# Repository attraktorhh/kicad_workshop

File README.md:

# KiCAD Workshop

Slides und Proketdateien für den Workshop 'Platinendesign mit KiCAD'

## Ablauf

Der Workshop finded in 3 Teilen statt.

### Teil 1

Im ersten Teil wird der Schaltplan erstellt und Footprints zugeordnet.

### Teil 2

Bei zweiten Workshop wird aus dem Schaltplan, der in Teil 1 erstellt wurde, eine Platine designed.

### Teil 3

Bein dritten Termin dreht sich alles um die Erstellung von Produktionsdateien (Gerber, BOM, Pick&Place).

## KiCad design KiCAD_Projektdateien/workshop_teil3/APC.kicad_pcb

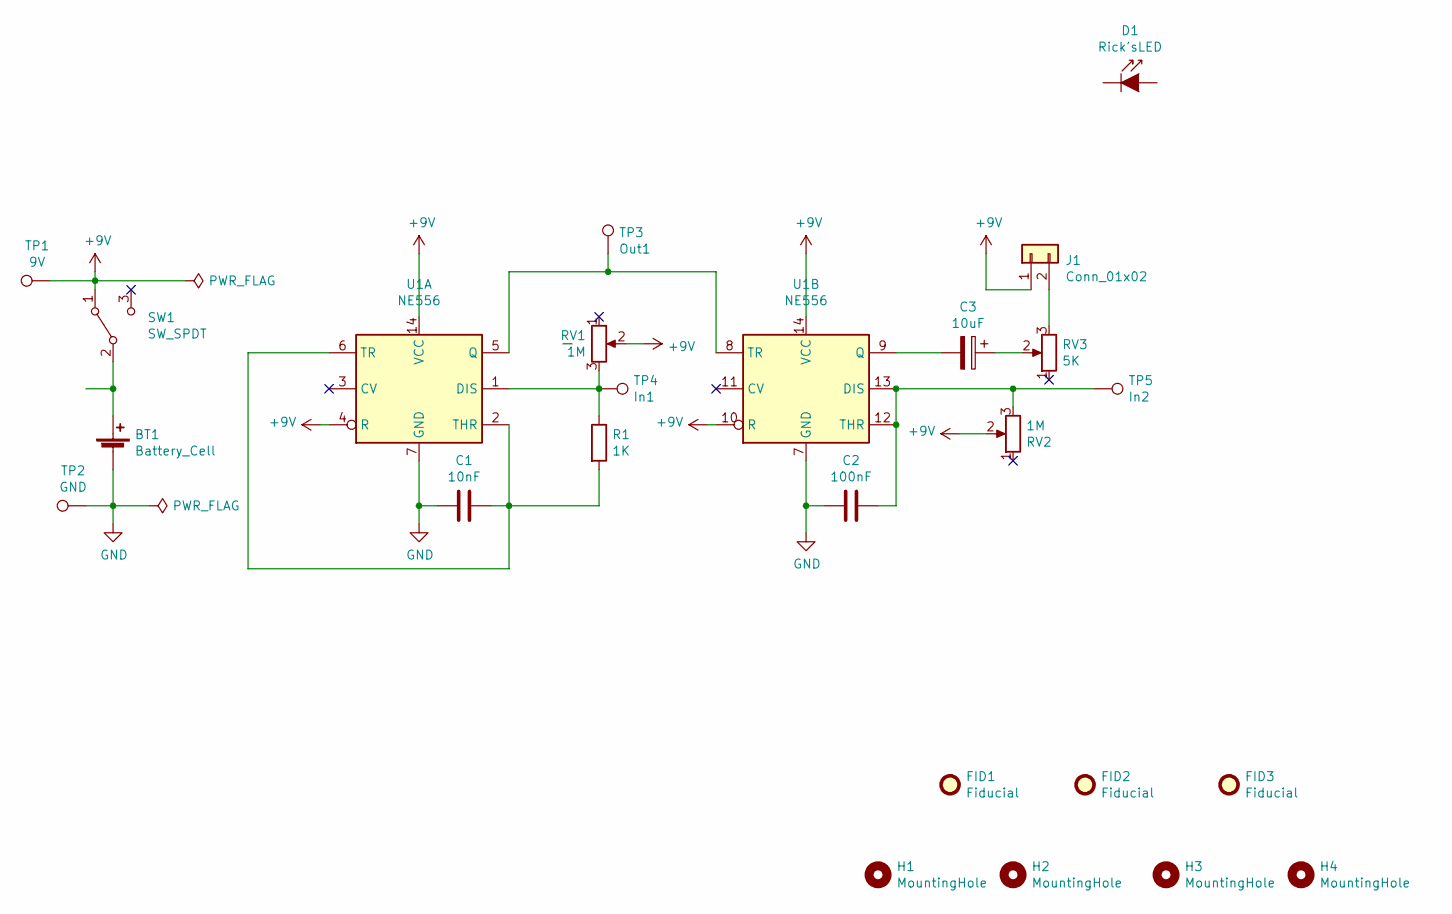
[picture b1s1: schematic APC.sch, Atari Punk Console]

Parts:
BT1: Battery_Cell; BatteryHolder_Eagle_12BH611-GR; Part Nr. 12BH611-GR
C1: 10nF; C_0603_1608Metric_Pad1.05x0.95mm_HandSolder; Part Nr. 885012206040
C2: 100nF; C_0603_1608Metric_Pad1.05x0.95mm_HandSolder; Part Nr. 885012206046
C3: 10uF; CP_Elec_5x3; Part Nr. 865080340001
D1: Rick'sLED; SOIC-12
FID1, FID2, FID3: Fiducial; Fiducial_1mm_Mask2mm
H1, H2, H3, H4: MountingHole; MountingHole_3.2mm_M3
J1: Conn_01x02; SolderWirePad_1x02_P7.62mm_Drill2.5mm
R1: 1K; R_0603_1608Metric_Pad1.05x0.95mm_HandSolder; Part Nr. ERJ-U02D7500X
RV1, RV2: 1M; Potentiometer_Bourns_PTV09A-1_Single_Vertical; Part Nr. PTV09A-4020U-B504
RV3: 5K; Potentiometer_Bourns_PTV09A-1_Single_Vertical; Part Nr. PTV09A-4020F-A502
SW1: SW_SPDT; SW_SPDT_CK-JS102011SAQN; Part Nr. JS102011SAQN
TP1: 9V; TestPoint_Pad_D1.5mm
TP2: GND; TestPoint_Pad_D1.5mm
TP3: Out1; TestPoint_Pad_D1.5mm
TP4: In1; TestPoint_Pad_D1.5mm
TP5: In2; TestPoint_Pad_D1.5mm
U1: NE556; SOIC-14_3.9x8.7mm_P1.27mm; Part Nr. NE556DR

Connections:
+9V: J1.1, RV1.2, RV2.2, SW1.1 (A), TP1.1, U1.4 (R), U1.10 (R), U1.14 (VCC)
GND: BT1.2 (-), C1.1, C2.2, TP2.1, U1.7 (GND)
unnamed: BT1.1 (+), SW1.2 (B)
unnamed: C1.2, R1.2, U1.2 (THR), U1.6 (TR)
unnamed: C2.1, RV2.3, TP5.1, U1.12 (THR), U1.13 (DIS)
unnamed: C3.1, RV3.2
unnamed: C3.2, U1.9 (Q)
unnamed: J1.2, RV3.3
unnamed: R1.1, RV1.3, TP4.1, U1.1 (DIS)
unnamed: TP3.1, U1.5 (Q), U1.8 (TR)

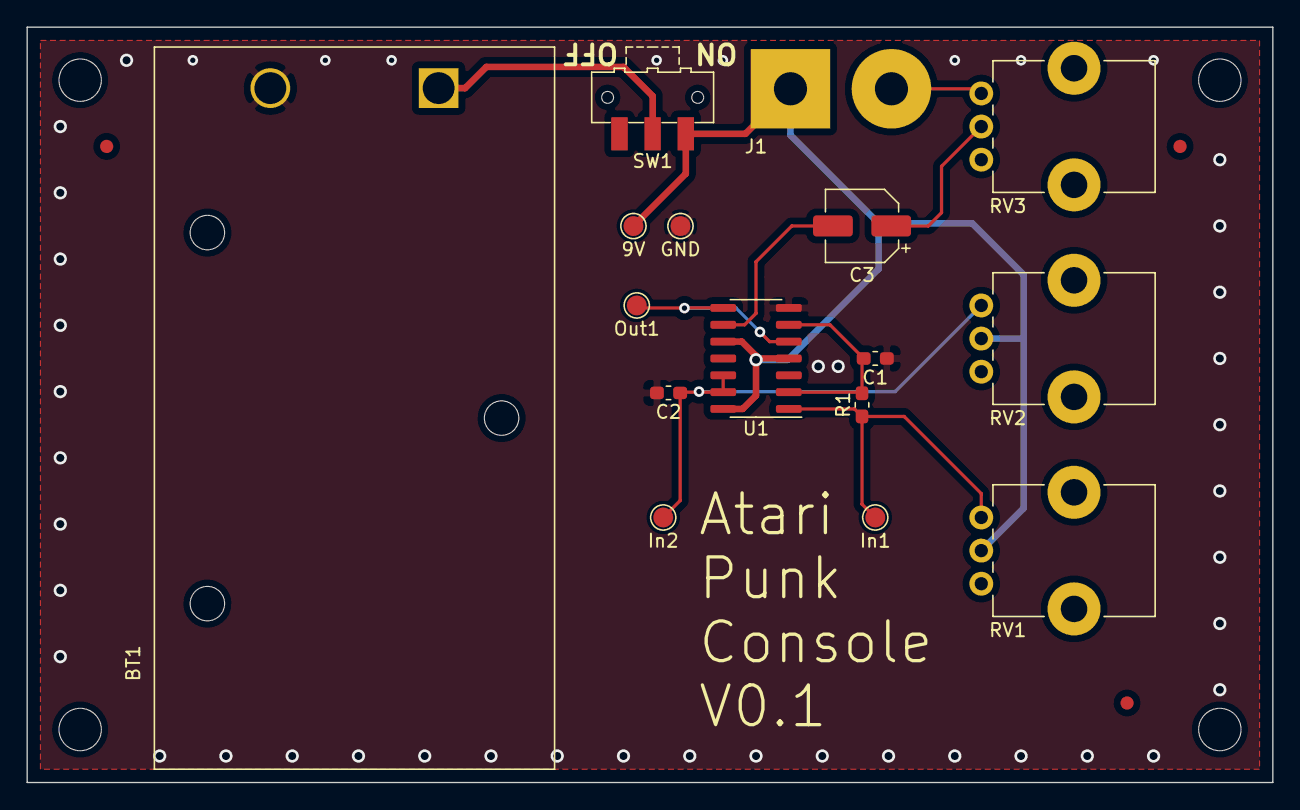
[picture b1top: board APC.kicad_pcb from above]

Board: 2 copper layers, 94.0 x 57.0 mm, 23 parts (0 on the bottom side), 10 nets.

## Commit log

2019-09-29 Added files for workshop3
2019-09-29 Created fabrication files
2019-09-29 renaming stuff
2019-09-29 renaming stuff
    mend
2019-09-30 Added fabrication files
2019-10-03 Files for workshop3; Fixed typo in teil2 slides
2019-10-03 Added slides for part 3
2019-10-05 Small fixes; added BOM
